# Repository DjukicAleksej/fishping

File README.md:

# FishPing

FishPing is a smart fishing float made by me, **Aleksej**, a 17 year old from Bosnia and Herzegovina. It is a custom hardware project with a 3D printed float body, a custom PCB, a Seeed Studio XIAO nRF52840, and a LIS3DH accelerometer that can detect when a fish pulls on the float.

The idea is simple: sometimes when you are fishing you look away for a second, talk to someone, check your phone, or just miss a small bite. FishPing watches the movement of the float and sends a BLE alert to your phone, where a small webpage shows the bite count, the time between bites, battery info, and an alarm.

I wanted this project to be a mix of real outdoor usefulness and hardware learning. It pushed me through PCB design, firmware, BLE, 3D enclosure design, waterproofing considerations, and making a phone interface without needing to write a full Android app.

---

## Zine Design

I also made a magazine style design for the Hack Club Magazine of projects.

---

## Quick Links

- [Firmware](firmware/FishPing_Firmware)
- [Phone web app](firmware/web)
- [PCB files](PCB_Files)
- [3D STEP files](3D_Files)
- [PCB BOM](BOM/BOM.csv)
- [Gerbers](PCB_Files/Gerbers.zip)

---

## Features

- Detects fish pulls using the **LIS3DH 3-axis accelerometer**
- Counts total bites
- Tracks the time since the last bite
- Tracks the interval between bites
- Sends bite events over **Bluetooth Low Energy**
- Android Chrome webpage for connecting to the float
- Phone alarm + vibration when a bite is detected
- Sensitivity and cooldown tuning from the webpage
- Battery-powered PCB with a physical power switch
- 3D printed enclosure with separate battery holder and PCB mounting posts

---

## Case Gallery
Case was designed using Onshape, here is the document link to the OnShape Project. <a href="https://cad.onshape.com/documents/5058fab60298abed43f40cc7/w/999f0f19ac49830b5a18ad7c/e/33939858eac56f5636a0ee71">OnShape Project Link</a>
| Front | Bottom |
| :---: | :---: |
|  |  |

| Exploded View |
| :---: |
|  |

---

## PCB Gallery

| PCB Front | PCB Back |
| :---: | :---: |
|  |  |

| 3D PCB Front | 3D PCB Back |
| :---: | :---: |
|  |  |

### Schematic

---

## How It Works

The float has a **LIS3DH accelerometer** connected to the XIAO nRF52840 over I2C. The firmware samples motion data and looks for sharp changes in acceleration that match the kind of movement a bite creates.

When a bite is detected, the firmware:

1. Increases the bite counter
2. Stores the time of the bite
3. Calculates the interval from the previous bite
4. Blinks the onboard/external status LED
5. Sends a BLE update to the phone

The phone webpage connects over Web Bluetooth, receives those stats, and rings/vibrates when a new bite event comes in.

---

## Repository Contents

| Path | What it contains |
| --- | --- |
| [`firmware/FishPing_Firmware`](firmware/FishPing_Firmware) | Arduino firmware for the XIAO nRF52840 |
| [`firmware/web`](firmware/web) | Android Chrome Web Bluetooth dashboard |
| [`Images`](Images) | Case renders, PCB renders, and schematic image |
| [`PCB_Files`](PCB_Files) | KiCad PCB/schematic files and Gerbers |
| [`3D_Files`](3D_Files) | STEP files for the printed enclosure |
| [`BOM`](BOM) | PCB bill of materials |
| [`tests`](tests) | Optional JavaScript tests for the web app and detector simulator |
| [`tools`](tools) | Bite detector simulator used by the tests |

---

## Build BOM

These are the extra mechanical parts needed for assembling the printed enclosure. This table does not include the PCB components from `BOM/BOM.csv`.

| Item | Quantity | Used for |
| --- | ---: | --- |
| M2 heat-set inserts | 4+ | Battery enclosure and PCB mounting stands |
| M2 x 6mm screws | 2 | Screwing the battery enclosure into the bottom part |
| M2 x 16mm screws | 2 | Screwing the PCB into the long internal stands |
| M3 heat-set inserts | 2 | Connecting the top and bottom float shell |
| M3 x 12mm screws | 2 | Screwing the top part into the bottom part |

Having a few spare inserts is useful because heat-set inserts are easy to overheat or press in slightly crooked.

---

## PCB BOM

This is the main PCB parts BOM from [`BOM/BOM.csv`](BOM/BOM.csv), with the battery added separately. Prices are from the time I exported the BOM, so check them again before ordering because component prices can move around.

| Item | Value | Quantity | LCSC # | Datasheet | Purchase link | Price |
| --- | --- | ---: | --- | --- | --- | ---: |
| Unpolarized capacitor | 1uF | 1 | C141772 | [Datasheet](https://www.lcsc.com/datasheet/C141772.pdf) | [Buy from LCSC](https://www.lcsc.com/product-detail/C141772.html) | $0.49 |
| Unpolarized capacitor | 100nF | 1 | C49678 | [Datasheet](https://www.lcsc.com/datasheet/C49678.pdf) | [Buy from LCSC](https://www.lcsc.com/product-detail/C49678.html) | $0.71 |
| Light emitting diode | LED | 1 | C2297 | [Datasheet](https://www.lcsc.com/datasheet/C2297.pdf) | [Buy from LCSC](https://www.lcsc.com/product-detail/C2297.html) | $0.82 |
| Generic connector, single row, 01x02 | Conn_01x02 | 1 | C160352 | [Datasheet](https://www.lcsc.com/datasheet/C160352.pdf) | [Buy from LCSC](https://www.lcsc.com/product-detail/C160352.html) | $1.72 |
| Resistor | 4.7k | 2 | C17673 | [Datasheet](https://www.lcsc.com/datasheet/C17673.pdf) | [Buy from LCSC](https://www.lcsc.com/product-detail/C17673.html) | $1.29 |
| Resistor | 220 | 1 | C17557 | [Datasheet](https://www.lcsc.com/datasheet/C17557.pdf) | [Buy from LCSC](https://www.lcsc.com/product-detail/C17557.html) | $0.47 |
| Single Pole Single Throw (SPST) switch | SW_SPST | 1 | C431541 | [Datasheet](https://www.lcsc.com/datasheet/C431541.pdf) | [Buy from LCSC](https://www.lcsc.com/product-detail/C431541.html) | $0.58 |
| 3-Axis Accelerometer | LIS3DH | 1 | C15134 | [Datasheet](https://www.st.com/resource/en/datasheet/cd00274221.pdf) | [Buy from LCSC](https://www.lcsc.com/product-detail/C15134.html) | $1.61 |
| Seeed Studio XIAO nRF52840 | XIAO-nRF52840-SMD | 1 | N/A | [Datasheet](https://files.seeedstudio.com/wiki/XIAO-BLE/nRF52840_PS_v1.5.pdf) | [Buy from AliExpress](https://www.aliexpress.com/item/1005006988954136.html) | $12.34 |
| Lithium Ion Polymer Battery | 3.7V 100mAh | 1 | N/A | [Datasheet](https://cdn-shop.adafruit.com/product-files/1570/1570datasheet.pdf) | [Buy from Adafruit](https://www.adafruit.com/product/1570) | $5.95 |
| **Total** |  | **11** |  |  |  | **$25.98** |

---

## Assembly

### 1. Print and prepare the parts

Print the top part, bottom part, and battery enclosure from the files in [`3D_Files`](3D_Files). Clean up any stringing or rough edges around the screw holes before installing inserts.

### 2. Install the battery

Place the battery into its space in the bottom part. After the battery is sitting properly, put the battery enclosure over it so it locks the battery in place.

Install **M2 heat-set inserts** into the marked holes for the battery enclosure, then use **M2 x 6mm screws** to screw the battery enclosure into place.

### 3. Mount the PCB

Install **M2 heat-set inserts** into the long PCB mounting stands. Try to keep the inserts straight, because the PCB holes need to line up cleanly.

Place the PCB into the bottom part so the screw holes align with the stands. Use **M2 x 16mm screws** to lock the PCB down.

### 4. Close the float

Install **M3 heat-set inserts** into the bottom part from the bottom side, in the marked holes used to connect the top and bottom shell.

Place the top part onto the bottom part and use **M3 x 12mm screws** to screw the top shell into the bottom shell.

### 5. Waterproof it

After everything is assembled, add a waterproof coating around the float to make it safer around water. Pay extra attention to seams, screw holes, and any possible gaps around the enclosure.

Do not skip this step. It is still an electronics project sitting in water, so the mechanical seal matters a lot.

---

## Firmware Setup

The firmware is written for the **Seeed Studio XIAO nRF52840** in the Arduino IDE.

### Required Arduino setup

1. Install the Arduino IDE.
2. Open **File > Preferences**.
3. Add this URL to **Additional Boards Manager URLs**:

   ```text
   https://files.seeedstudio.com/arduino/package_seeeduino_boards_index.json
   ```

4. Open **Tools > Board > Boards Manager**.
5. Install the **Seeed nRF52 Boards** package.
6. Open **Library Manager** and install:

   - `ArduinoBLE`

The firmware also uses `Wire`, which is included with Arduino, so you do not need a separate LIS3DH library. The LIS3DH code is included in this repo as `Lis3dhMinimal.h`.

### Uploading

1. Open [`firmware/FishPing_Firmware/FishPing_Float.ino`](firmware/FishPing_Firmware/FishPing_Float.ino).
2. Select the Seeed XIAO nRF52840 board in Arduino IDE.
3. Select the correct USB port.
4. Click **Verify**.
5. Click **Upload**.

If upload fails, double-tap reset on the XIAO to put it into bootloader mode, then upload again.

---

## Phone Web App Setup
The easiest way to use the web page is accessing it using the link - https://fishping.vercel.app/ , I host it on vercel so you can access it for free and use it at your will, if you want to self host it here's how to do it:

The phone side is a simple webpage inside [`firmware/web`](firmware/web). It uses **Web Bluetooth**, so it works best on **Android Chrome**.

No npm packages are required for the actual webpage.

To test it locally on a computer:

```powershell
python -m http.server 8080 -d firmware/web
```

Then open:

```text
http://localhost:8080
```

For Android use, host the `firmware/web` folder somewhere with HTTPS, like GitHub Pages, Netlify, or Cloudflare Pages. Web Bluetooth needs HTTPS on real phones.

---

## How To Use FishPing

1. Charge/connect the battery.
2. Turn on the small switch on the PCB. The board will not consume/use battery power until this switch is on.
3. Open the FishPing webpage on Android Chrome.
4. Tap **Connect**.
5. Select **FishPing Float** from the Bluetooth device list.
6. Tap **Test alarm** once so the browser is allowed to play sound.
7. Put the float in water and use **Calibrate** when it is sitting normally.
8. Start fishing.

If the float triggers too easily from waves, lower the sensitivity or increase cooldown. If it misses small bites, increase sensitivity.

---

## BLE Details

The firmware advertises as:

```text
FishPing Float
```

Main BLE service:

```text
f15bb8d0-7a6f-4f3c-9a91-0fd76a6f1000
```

| Characteristic | UUID suffix | Direction | What it does |
| --- | --- | --- | --- |
| Stats | `1001` | Read / notify | Sends bite count, timing, battery, sensitivity, and sensor status |
| Event | `1002` | Read / notify | Changes whenever a new bite is detected |
| Command | `1003` | Write | Receives commands from the webpage |

Supported commands:

| Command | Meaning |
| --- | --- |
| `RESET` | Clears bite count and timing |
| `ARM` | Enables bite detection |
| `DISARM` | Pauses bite detection |
| `CAL` | Re-learns the normal resting motion baseline |
| `SENS=1..10` | Sets detection sensitivity |
| `COOLDOWN=500..30000` | Sets minimum time between counted bites |

---

## Notes

- The LIS3DH is expected at I2C address `0x18`, but the firmware also checks `0x19`.
- The status LED is on `D9`.
- The LIS3DH interrupt pin is connected to `D0`, but the current firmware detects bites in software from sampled motion data.
- Web Bluetooth does not work in iPhone Safari, which is why this version targets Android Chrome.
- Waterproofing is part of the build, not just decoration. Coat and test carefully before trusting it in water.

---

Built by **Aleksej Djukic**.

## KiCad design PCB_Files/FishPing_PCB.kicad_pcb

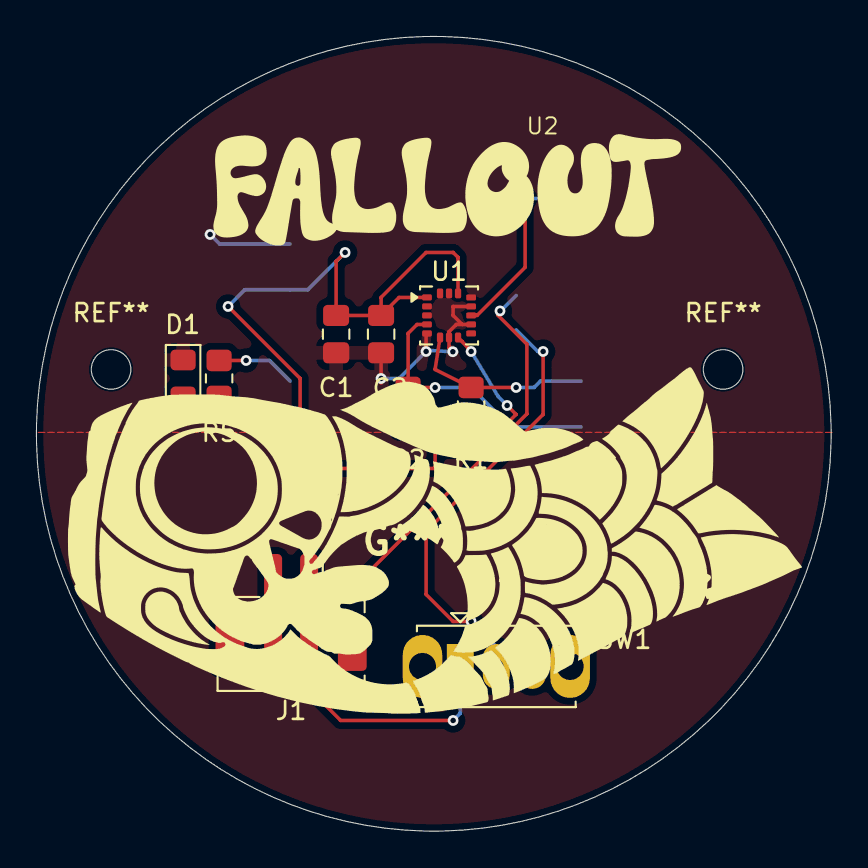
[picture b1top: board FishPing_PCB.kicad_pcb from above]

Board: 2 copper layers, 44.1 x 44.1 mm, 10 parts (1 on the bottom side), 10 nets.

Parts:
C1: 1uF; C_0805_2012Metric_Pad1.18x1.45mm_HandSolder
C2: 100nF; C_0805_2012Metric_Pad1.18x1.45mm_HandSolder
D1: LED; LED_0805_2012Metric_Pad1.15x1.40mm_HandSolder
J1: Conn_01x02; JST_PH_B2B-PH-SM4-TB_1x02-1MP_P2.00mm_Vertical
R1, R2: 4.7k; R_0805_2012Metric_Pad1.20x1.40mm_HandSolder
R5: 220; R_0805_2012Metric_Pad1.20x1.40mm_HandSolder
SW1: SW_SPST; SW_Slide_SPDT_Straight_CK_OS102011MS2Q
U1: LIS3DH; LGA-16_3x3mm_P0.5mm_LayoutBorder3x5y
U2: XIAO-nRF52840-SMD

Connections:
+3V3: C1.1, C2.1, R1.1, R2.1, U1.1 (VDD_IO), U1.8 (CS), U1.14 (VDD), U2.11 (3V3_12)
+BATT: SW1.2 (B), U2.19
-BATT: J1.1, U2.20
GND: C1.2, C2.2, D1.1 (K), U1.5 (GND), U1.7 (SDO), U1.10 (GND), U1.12 (GND), U2.12 (GND_13)
INT: U1.11 (INT1), U2.0 (P0.02_A0_D0_1)
unnamed: D1.2 (A), R5.1
unnamed: J1.2, SW1.1 (A)
unnamed: R5.2, U2.9 (P1.14_D9_MISO_10)
SCL: R2.2, U1.4 (SPC), U2.5 (P0.05_A5_D5_SCL_6)
SDA: R1.2, U1.6 (SDI), U2.4 (P0.04_A4_D4_SDA_5)

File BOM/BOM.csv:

Item,Value,Datasheet,LCSC #,Quantity,MOQ,Cost
Unpolarized capacitor,1uF,https://www.lcsc.com/datasheet/C141772.pdf,C141772,1,10,$0.49 
Unpolarized capacitor,100nF,https://www.lcsc.com/datasheet/C49678.pdf,C49678,1,20,$0.71 
Light emitting diode,LED,https://www.lcsc.com/datasheet/C2297.pdf,C2297,1,50,$0.82 
"Generic connector, single row, 01x02",Conn_01x02,https://www.lcsc.com/datasheet/C160352.pdf,C160352,1,5,$1.72 
Resistor,4.7k,https://www.lcsc.com/datasheet/C17673.pdf,C17673,2,100,$1.29 
Resistor,220,https://www.lcsc.com/datasheet/C17557.pdf,C17557,1,100,$0.47 
Single Pole Single Throw (SPST) switch,SW_SPST,https://www.lcsc.com/datasheet/C431541.pdf,C431541,1,10,$0.58 
3-Axis Accelerometer,LIS3DH,https://www.st.com/resource/en/datasheet/cd00274221.pdf,C15134,1,1,$1.61 
Seeed Studio Xiao nRF52840,XIAO-nRF52840-SMD,https://files.seeedstudio.com/wiki/XIAO-BLE/nRF52840_PS_v1.5.pdf,AliExpress Link: https://www.aliexpress.com/item/1005006988954136.html,1,1,$12.34 
Total,,,,10,297,$20.03
